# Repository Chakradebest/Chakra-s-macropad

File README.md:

# Chakra's pad Project

## 1. Overall Hackpad

## 2. Schematic

## 3. PCB Layout

## 4. Case and Assembly

## 5. Bill of Materials (BOM)
[Click here to view my BOM](bom.csv)

## How it Works
* **Brain:** XIAO RP2040.
* **Buttons:** 6 keys handled by an MCP23017 I/O Expander.
* **Extras:** Dual rotary encoders and an OLED display.

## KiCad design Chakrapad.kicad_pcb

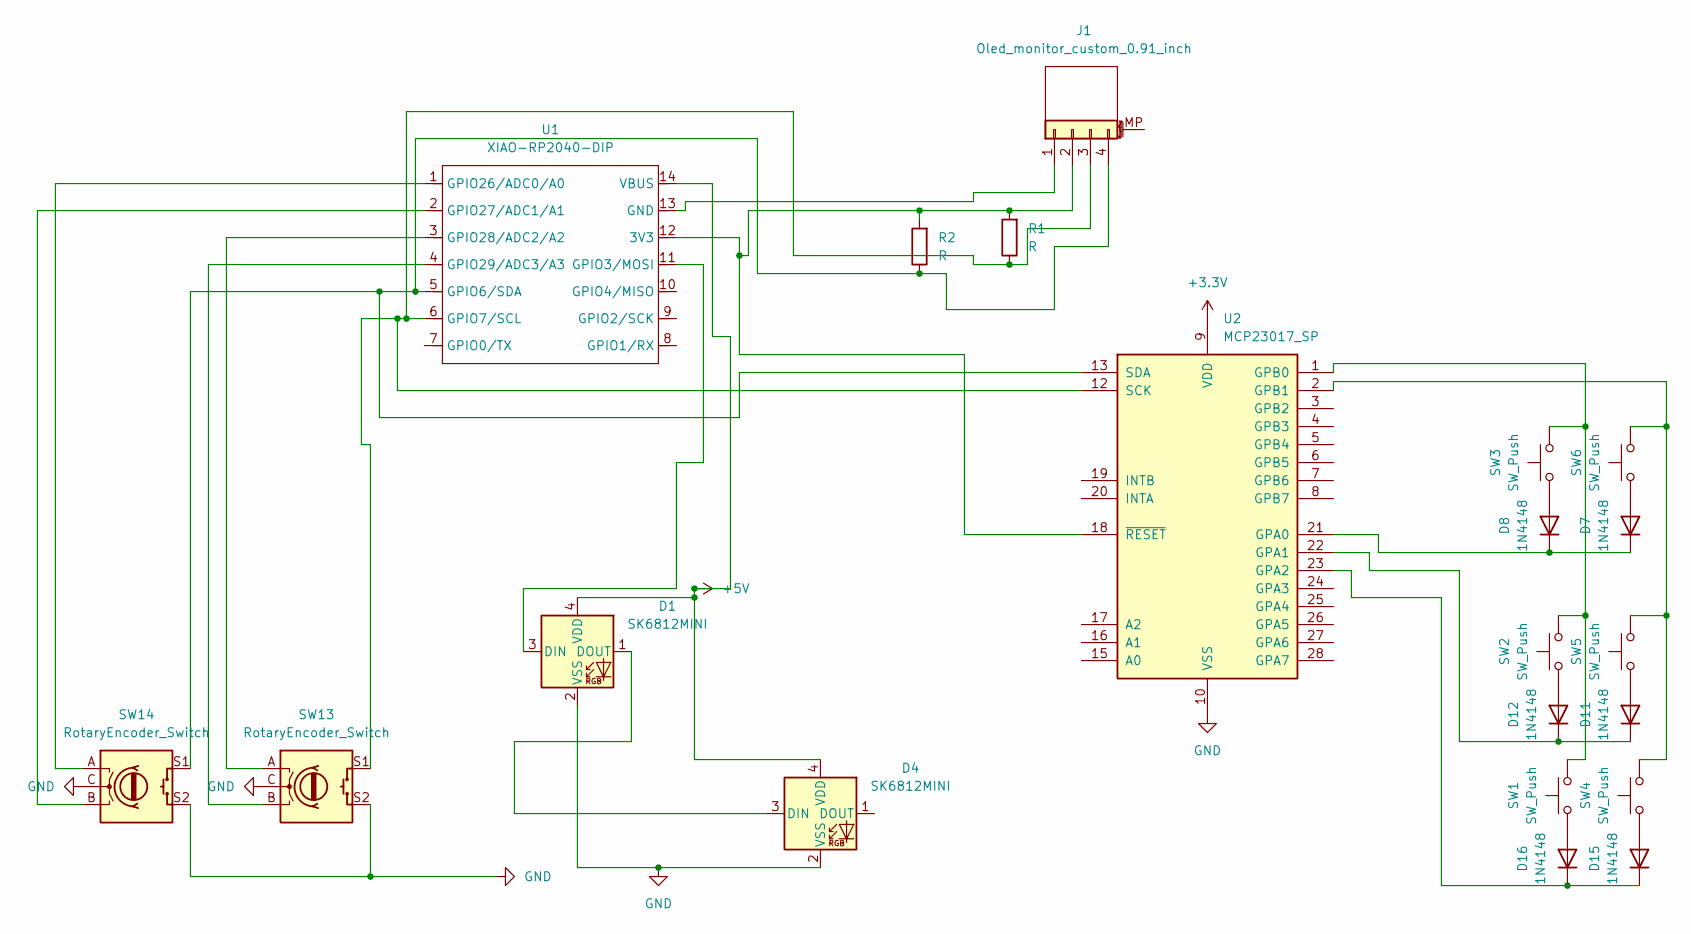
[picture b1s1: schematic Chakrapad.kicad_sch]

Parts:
D1, D4: SK6812MINI; LED_SK6812MINI_PLCC4_3.5x3.5mm_P1.75mm
D7, D8, D11, D12, D15, D16: 1N4148; D_DO-35_SOD27_P7.62mm_Horizontal
J1: Oled_monitor_custom_0.91_inch; SSD1306-0.91-OLED-4pin-128x32
R1, R2: R; R_Axial_DIN0207_L6.3mm_D2.5mm_P7.62mm_Horizontal
SW1, SW2, SW3, SW4, SW5, SW6: SW_Push; SW_Cherry_MX_1.00u_PCB
SW13, SW14: RotaryEncoder_Switch; RotaryEncoder_Alps_EC11E-Switch_Vertical_H20mm_MountingHoles
U1: XIAO-RP2040-DIP
U2: MCP23017_SP; DIP-28_W7.62mm

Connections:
+3.3V: U2.9 (VDD)
+5V: D1.4 (VDD), D4.4 (VDD), U1.14 (VBUS)
GND: D1.2 (VSS), D4.2 (VSS), SW13.C, SW13.S2, SW14.C, SW14.S2, U2.10 (VSS)
unnamed: D1.3 (DIN), U1.11 (GPIO3/MOSI)
unnamed: D1.1 (DOUT), D4.3 (DIN)
unnamed: D7.2 (A), SW6.1
unnamed: D7.1 (K), D8.1 (K), U2.21 (GPA0)
unnamed: D8.2 (A), SW3.1
unnamed: D11.2 (A), SW5.1
unnamed: D11.1 (K), D12.1 (K), U2.22 (GPA1)
unnamed: D12.2 (A), SW2.1
unnamed: D15.2 (A), SW4.1
unnamed: D15.1 (K), D16.1 (K), U2.23 (GPA2)
unnamed: D16.2 (A), SW1.1
unnamed: J1.1 (GND), U1.13 (GND)
unnamed: J1.3 (SCL), R1.1, SW13.S1, U1.6 (GPIO7/SCL), U2.12 (SCK)
unnamed: J1.4 (SDA), R2.1, SW14.S1, U1.5 (GPIO6/SDA), U2.13 (SDA)
unnamed: J1.2 (VCC), R1.2, R2.2, U1.12 (3V3), U2.18 (~RESET)
unnamed: SW14.A, U1.1 (GPIO26/ADC0/A0)
unnamed: SW14.B, U1.2 (GPIO27/ADC1/A1)
unnamed: SW13.A, U1.3 (GPIO28/ADC2/A2)
unnamed: SW13.B, U1.4 (GPIO29/ADC3/A3)
unnamed: SW1.2, SW2.2, SW3.2, U2.1 (GPB0)
unnamed: SW4.2, SW5.2, SW6.2, U2.2 (GPB1)

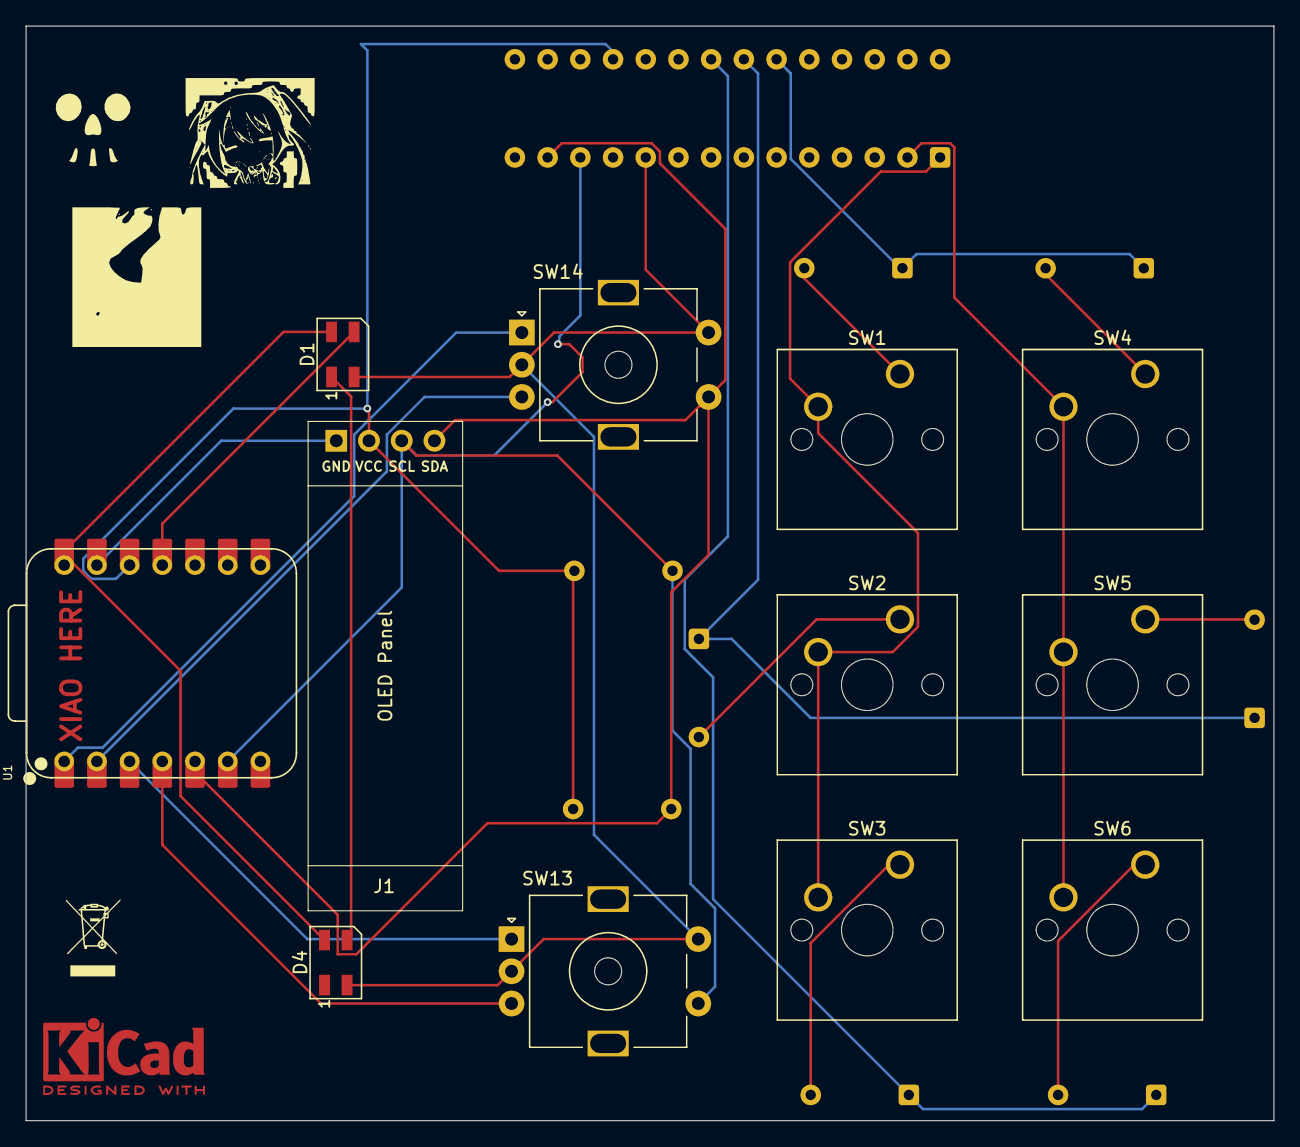
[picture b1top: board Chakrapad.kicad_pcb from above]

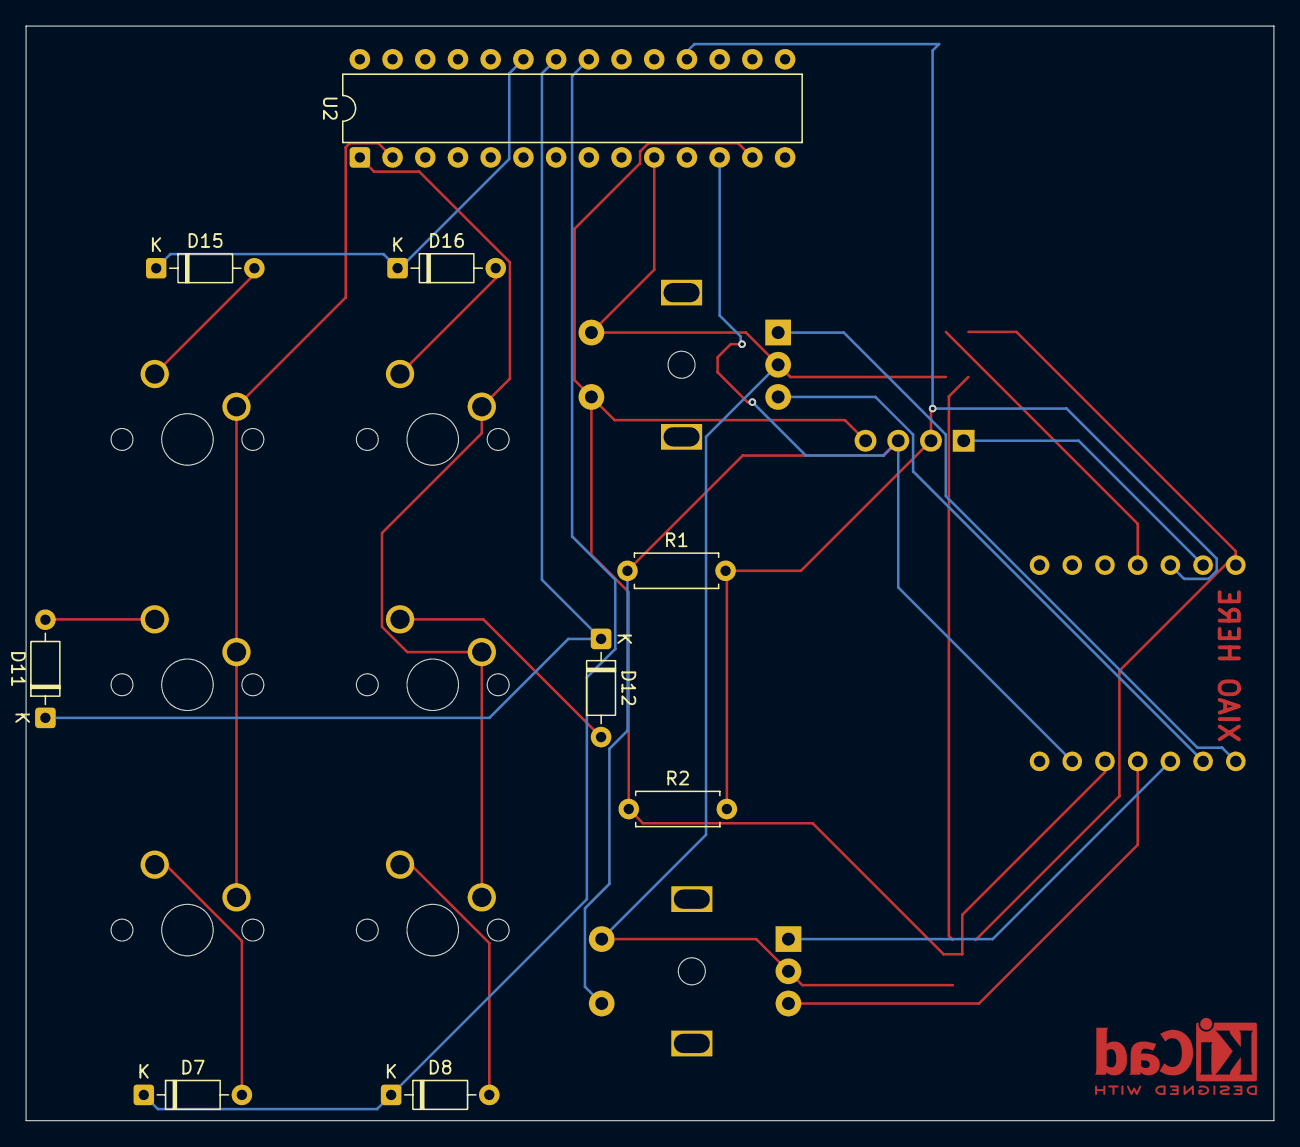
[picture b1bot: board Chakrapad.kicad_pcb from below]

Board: 2 copper layers, 96.9 x 85.0 mm, 21 parts (9 on the bottom side), 23 nets.

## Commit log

2026-01-17 Rename Chakrapad.kicad_pro to PCB/Chakrapad.kicad_pro
2026-01-17 Rename Full case assembeled.step to CAD/Full case assembeled.step
